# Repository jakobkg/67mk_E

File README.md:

# 67mk_E

[![CC BY-NC-SA 4.0][cc-by-nc-sa-shield]][cc-by-nc-sa]

### A simple "no frills" drop-in replacement PCB for the KBDfans 67mkII / 67lite

---

[KiCAD PCB files](pcb/)

[Gerbers for PCB production](pcb/gerbers/)

[JLCPCB BOM](pcb/fab/67_E_bom_jlc.csv)

[JLCPCB CPL](pcb/fab/67_E_cpl_jlc.csv)

[Vial-QMK firmware](firmware/)

---

---

This work is licensed under a
[Creative Commons Attribution-NonCommercial-ShareAlike 4.0 International License][cc-by-nc-sa].

[![CC BY-NC-SA 4.0][cc-by-nc-sa-image]][cc-by-nc-sa]

[cc-by-nc-sa]: http://creativecommons.org/licenses/by-nc-sa/4.0/
[cc-by-nc-sa-image]: https://licensebuttons.net/l/by-nc-sa/4.0/88x31.png
[cc-by-nc-sa-shield]: https://img.shields.io/badge/License-CC%20BY--NC--SA%204.0-lightgrey.svg

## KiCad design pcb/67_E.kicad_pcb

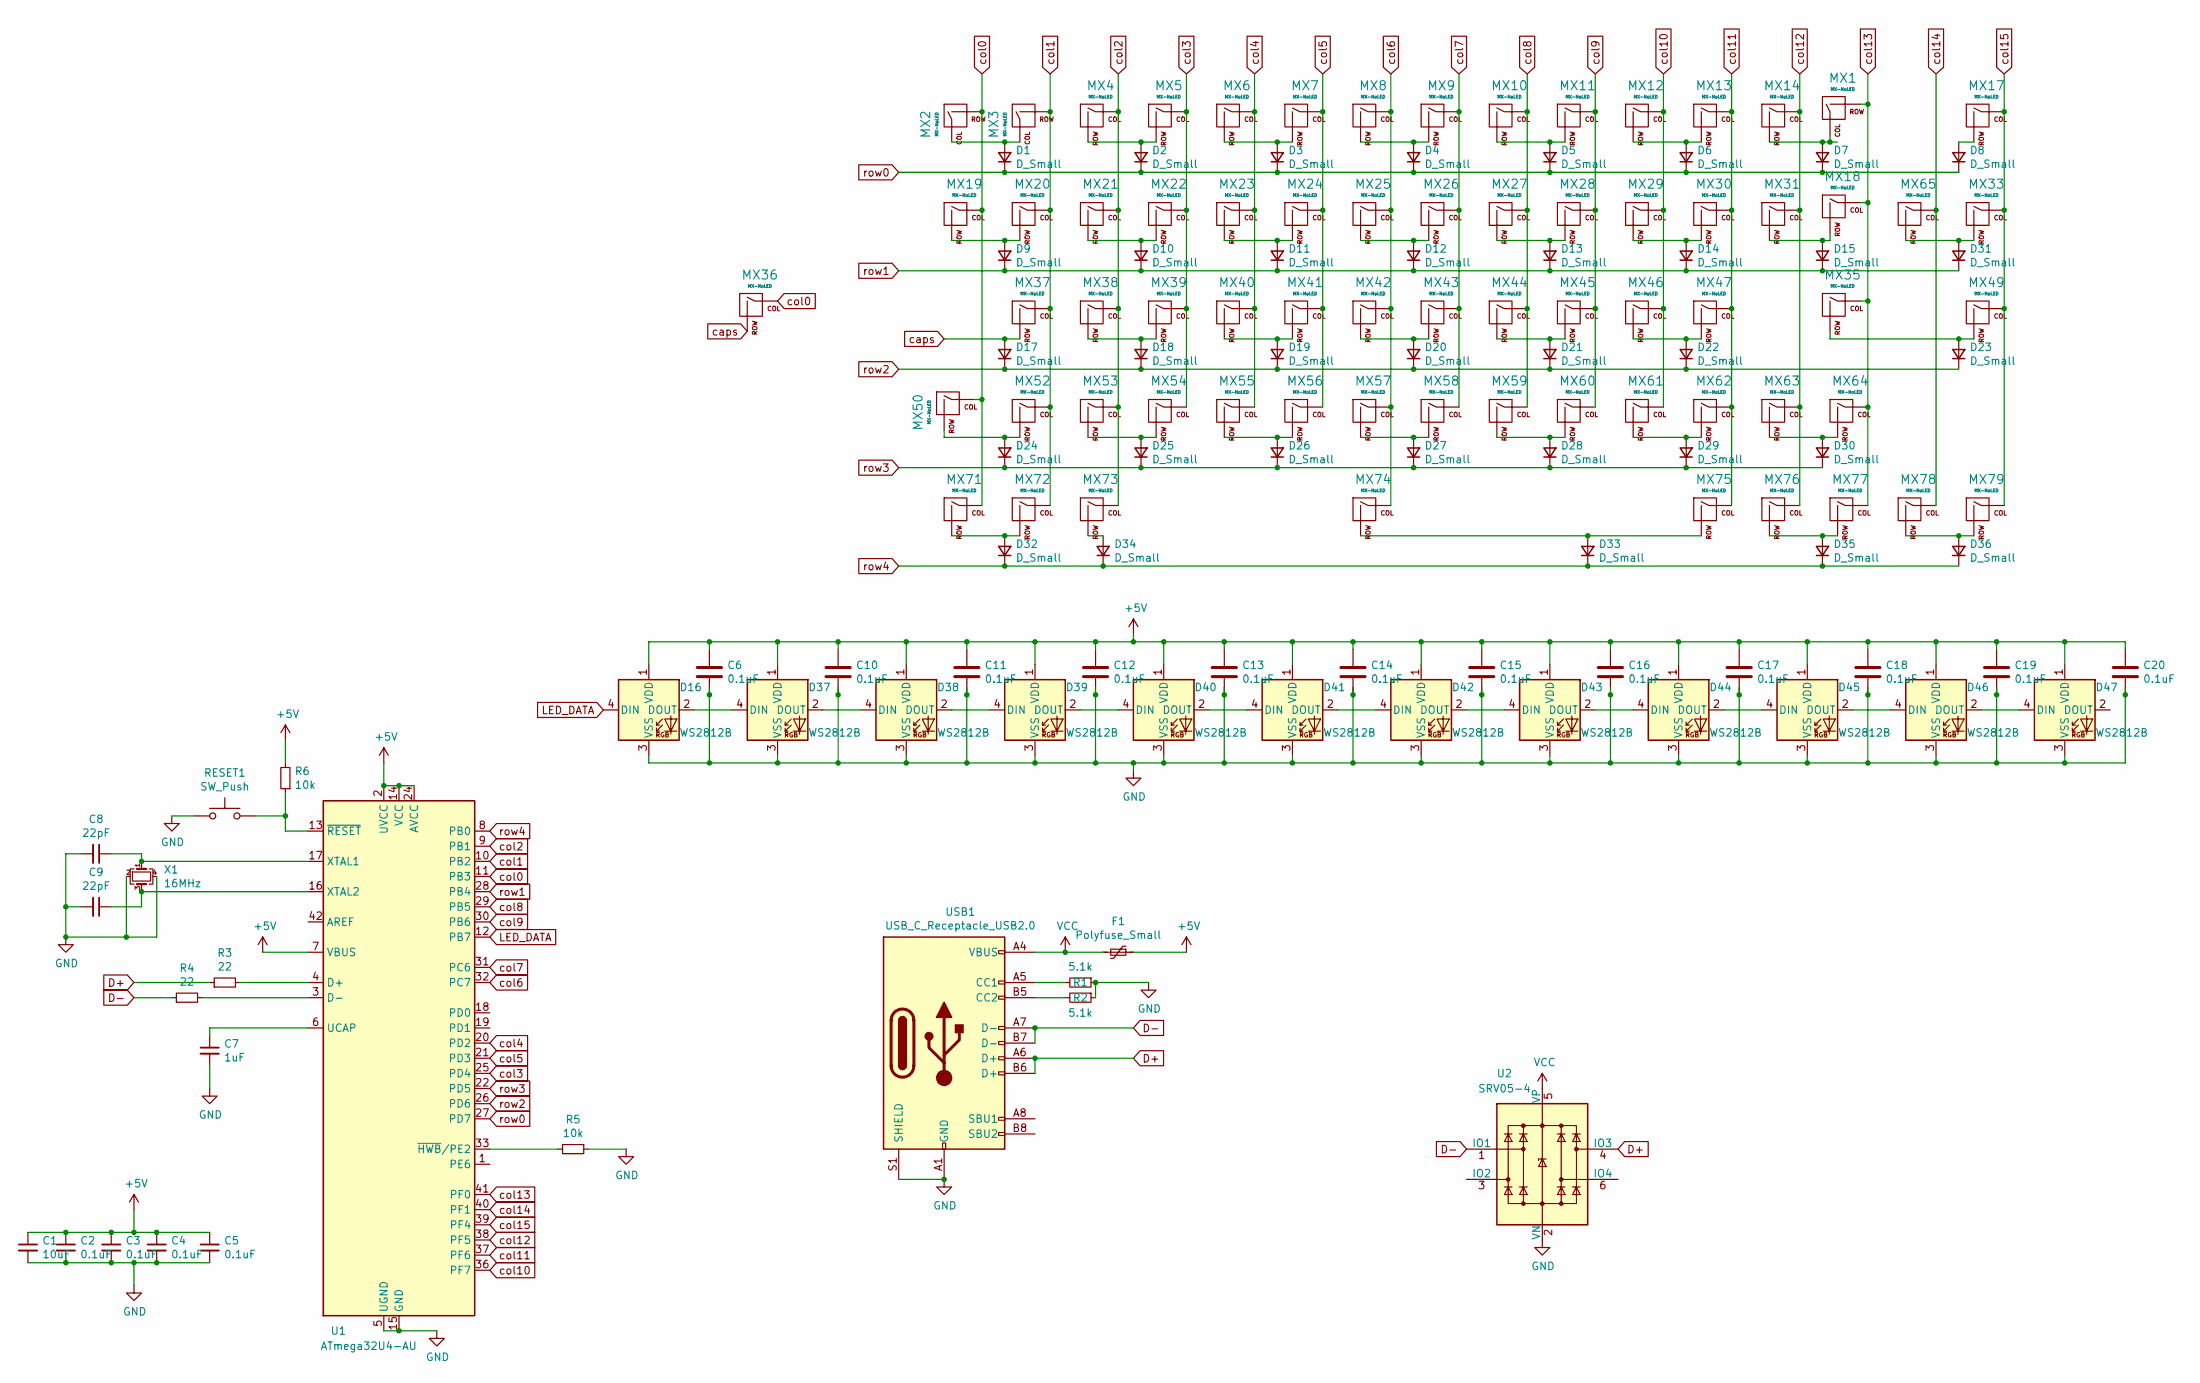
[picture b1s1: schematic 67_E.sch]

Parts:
C1: 10uF; C_0805_2012Metric; LCSC C91245
C2, C3, C4, C5: 0.1uF; C_0805_2012Metric; LCSC C49678
C6, C10, C11, C12, C13, C14, C15, C16, C17, C18, C19, C20: 0.1uF; C_0805_2012Metric
C7: 1uF; C_0805_2012Metric; LCSC C28323
C8, C9: 22pF; C_0805_2012Metric; LCSC C1804
D1, D2, D3, D4, D5, D6, D7, D8, D9, D10, D11, D12, D13, D14, D15, D17, D18, D19, D20, D21, D22, D23, D24, D25, D26, D27, D28, D29, D30, D31, D32, D33, D34, D35, D36: D_Small; D_SOT-23_ANK; LCSC C68978
D16, D37, D38, D39, D40, D41, D42, D43, D44, D45, D46, D47: WS2812B; LED_WS2812B_PLCC4_5.0x5.0mm_P3.2mm
F1: Polyfuse_Small; Fuse_1206_3216Metric; LCSC C69688
MX1: MX-NoLED; MXOnly-2U-Hotswap
MX2, MX3, MX4, MX5, MX6, MX7, MX8, MX9, MX10, MX11, MX12, MX13, MX14, MX17, MX18, MX20, MX21, MX22, MX23, MX24, MX25, MX26, MX27, MX28, MX29, MX30, MX31, MX33, MX37, MX38, MX39, MX40, MX41, MX42, MX43, MX44, MX45, MX46, MX47, MX49, MX52, MX53, MX54, MX55, MX56, MX57, MX58, MX59, MX60, MX61, MX62, MX64, MX65, MX77, MX78, MX79: MX-NoLED; MXOnly-1U-Hotswap
MX19: MX-NoLED; MXOnly-1.5U-Hotswap
MX35: MX-NoLED; MXOnly-ISO-Hotswap-ReversedStabilizers
MX36, MX63: MX-NoLED; MXOnly-1.75U-Hotswap
MX50, MX71, MX72, MX73, MX75, MX76: MX-NoLED; MXOnly-1.25U-Hotswap
MX74: MX-NoLED; MXOnly-6.25U-Hotswap-ReversedStabilizers
R1, R2: 5.1k; R_0805_2012Metric; LCSC C27834
R3, R4: 22; R_0805_2012Metric; LCSC C17561
R5, R6: 10k; R_0805_2012Metric; LCSC C17414
RESET1: SW_Push; TestPoint_2Pads_Pitch2.54mm_Drill0.8mm; LCSC C318884
U1: ATmega32U4-AU; TQFP-44_10x10mm_P0.8mm; LCSC C44854
U2: SRV05-4; SOT-23-6; LCSC C85364
USB1: USB_C_Receptacle_USB2.0; USB_C_Receptacle_HRO_TYPE-C-31-M-12; LCSC C165948
X1: 16MHz; Crystal_SMD_3225-4Pin_3.2x2.5mm; LCSC C13738

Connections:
+5V: C1.1, C2.1, C3.1, C4.1, C5.1, C6.1, C10.1, C11.1, C12.1, C13.1, C14.1, C15.1, C16.1, C17.1, C18.1, C19.1, C20.1, D16.1 (VDD), D37.1 (VDD), D38.1 (VDD), D39.1 (VDD), D40.1 (VDD), D41.1 (VDD), D42.1 (VDD), D43.1 (VDD), D44.1 (VDD), D45.1 (VDD), D46.1 (VDD), D47.1 (VDD), F1.1, R6.2, U1.2 (UVCC), U1.7 (VBUS), U1.14 (VCC), U1.24 (AVCC), U1.34 (VCC), U1.44 (AVCC)
D+: R3.1, U2.4 (IO3), USB1.A6 (D+), USB1.B6 (D+)
D-: R4.1, U2.1 (IO1), USB1.A7 (D-), USB1.B7 (D-)
GND: C1.2, C2.2, C3.2, C4.2, C5.2, C6.2, C7.2, C8.2, C9.2, C10.2, C11.2, C12.2, C13.2, C14.2, C15.2, C16.2, C17.2, C18.2, C19.2, C20.2, D16.3 (VSS), D37.3 (VSS), D38.3 (VSS), D39.3 (VSS), D40.3 (VSS), D41.3 (VSS), D42.3 (VSS), D43.3 (VSS), D44.3 (VSS), D45.3 (VSS), D46.3 (VSS), D47.3 (VSS), R1.1, R2.1, R5.1, RESET1.1, U1.5 (UGND), U1.15 (GND), U1.23 (GND), U1.35 (GND), U1.43 (GND), U2.2 (VN), USB1.A1 (GND), USB1.A12 (GND), USB1.B1 (GND), USB1.B12 (GND), USB1.S1 (SHIELD), X1.2, X1.4
LED_DATA: D16.4 (DIN), U1.12 (PB7)
unnamed: C7.1, U1.6 (UCAP)
unnamed: C8.1, U1.17 (XTAL1), X1.1
unnamed: C9.1, U1.16 (XTAL2), X1.3
unnamed: D1.2 (A), MX2.1 (COL), MX3.1 (COL)
unnamed: D2.2 (A), MX4.2 (ROW), MX5.2 (ROW)
unnamed: D3.2 (A), MX6.2 (ROW), MX7.2 (ROW)
unnamed: D4.2 (A), MX8.2 (ROW), MX9.2 (ROW)
unnamed: D5.2 (A), MX10.2 (ROW), MX11.2 (ROW)
unnamed: D6.2 (A), MX12.2 (ROW), MX13.2 (ROW)
unnamed: D7.2 (A), MX1.1 (COL), MX14.2 (ROW)
unnamed: D8.2 (A), MX17.2 (ROW)
unnamed: D9.2 (A), MX19.2 (ROW), MX20.2 (ROW)
unnamed: D10.2 (A), MX21.2 (ROW), MX22.2 (ROW)
unnamed: D11.2 (A), MX23.2 (ROW), MX24.2 (ROW)
unnamed: D12.2 (A), MX25.2 (ROW), MX26.2 (ROW)
unnamed: D13.2 (A), MX27.2 (ROW), MX28.2 (ROW)
unnamed: D14.2 (A), MX29.2 (ROW), MX30.2 (ROW)
unnamed: D15.2 (A), MX18.2 (ROW), MX31.2 (ROW)
unnamed: D16.2 (DOUT), D37.4 (DIN)
unnamed: D18.2 (A), MX38.2 (ROW), MX39.2 (ROW)
unnamed: D19.2 (A), MX40.2 (ROW), MX41.2 (ROW)
unnamed: D20.2 (A), MX42.2 (ROW), MX43.2 (ROW)
unnamed: D21.2 (A), MX44.2 (ROW), MX45.2 (ROW)
unnamed: D22.2 (A), MX46.2 (ROW), MX47.2 (ROW)
unnamed: D23.2 (A), MX35.2 (ROW), MX49.2 (ROW)
unnamed: D24.2 (A), MX50.2 (ROW), MX52.2 (ROW)
unnamed: D25.2 (A), MX53.2 (ROW), MX54.2 (ROW)
unnamed: D26.2 (A), MX55.2 (ROW), MX56.2 (ROW)
unnamed: D27.2 (A), MX57.2 (ROW), MX58.2 (ROW)
unnamed: D28.2 (A), MX59.2 (ROW), MX60.2 (ROW)
unnamed: D29.2 (A), MX61.2 (ROW), MX62.2 (ROW)
unnamed: D30.2 (A), MX63.2 (ROW), MX64.2 (ROW)
unnamed: D31.2 (A), MX33.2 (ROW), MX65.2 (ROW)
unnamed: D32.2 (A), MX71.2 (ROW), MX72.2 (ROW)
unnamed: D33.2 (A), MX74.2 (ROW), MX75.2 (ROW)
unnamed: D34.2 (A), MX73.2 (ROW)
unnamed: D35.2 (A), MX76.2 (ROW), MX77.2 (ROW)
unnamed: D36.2 (A), MX78.2 (ROW), MX79.2 (ROW)
unnamed: D37.2 (DOUT), D38.4 (DIN)
unnamed: D38.2 (DOUT), D39.4 (DIN)
unnamed: D39.2 (DOUT), D40.4 (DIN)
unnamed: D40.2 (DOUT), D41.4 (DIN)
unnamed: D41.2 (DOUT), D42.4 (DIN)
unnamed: D42.2 (DOUT), D43.4 (DIN)
unnamed: D43.2 (DOUT), D44.4 (DIN)
unnamed: D44.2 (DOUT), D45.4 (DIN)
unnamed: D45.2 (DOUT), D46.4 (DIN)
unnamed: D46.2 (DOUT), D47.4 (DIN)
unnamed: R1.2, USB1.A5 (CC1)
unnamed: R2.2, USB1.B5 (CC2)
unnamed: R3.2, U1.4 (D+)
unnamed: R4.2, U1.3 (D-)
unnamed: R5.2, U1.33 (~HWB~/PE2)
unnamed: R6.1, RESET1.2, U1.13 (~RESET)
VCC: F1.2, U2.5 (VP), USB1.A4 (VBUS), USB1.A9 (VBUS), USB1.B4 (VBUS), USB1.B9 (VBUS)
caps: D17.2 (A), MX36.2 (ROW), MX37.2 (ROW)
col0: MX2.2 (ROW), MX19.1 (COL), MX36.1 (COL), MX50.1 (COL), MX71.1 (COL), U1.11 (PB3)
col1: MX3.2 (ROW), MX20.1 (COL), MX37.1 (COL), MX52.1 (COL), MX72.1 (COL), U1.10 (PB2)
col2: MX4.1 (COL), MX21.1 (COL), MX38.1 (COL), MX53.1 (COL), MX73.1 (COL), U1.9 (PB1)
col3: MX5.1 (COL), MX22.1 (COL), MX39.1 (COL), MX54.1 (COL), U1.25 (PD4)
col4: MX6.1 (COL), MX23.1 (COL), MX40.1 (COL), MX55.1 (COL), U1.20 (PD2)
col5: MX7.1 (COL), MX24.1 (COL), MX41.1 (COL), MX56.1 (COL), U1.21 (PD3)
col6: MX8.1 (COL), MX25.1 (COL), MX42.1 (COL), MX57.1 (COL), MX74.1 (COL), U1.32 (PC7)
col7: MX9.1 (COL), MX26.1 (COL), MX43.1 (COL), MX58.1 (COL), U1.31 (PC6)
col8: MX10.1 (COL), MX27.1 (COL), MX44.1 (COL), MX59.1 (COL), U1.29 (PB5)
col9: MX11.1 (COL), MX28.1 (COL), MX45.1 (COL), MX60.1 (COL), U1.30 (PB6)
col10: MX12.1 (COL), MX29.1 (COL), MX46.1 (COL), MX61.1 (COL), U1.36 (PF7)
col11: MX13.1 (COL), MX30.1 (COL), MX47.1 (COL), MX62.1 (COL), MX75.1 (COL), U1.37 (PF6)
col12: MX14.1 (COL), MX31.1 (COL), MX63.1 (COL), MX76.1 (COL), U1.38 (PF5)
col13: MX1.2 (ROW), MX18.1 (COL), MX35.1 (COL), MX64.1 (COL), MX77.1 (COL), U1.41 (PF0)
col14: MX65.1 (COL), MX78.1 (COL), U1.40 (PF1)
col15: MX17.1 (COL), MX33.1 (COL), MX49.1 (COL), MX79.1 (COL), U1.39 (PF4)
row0: D1.1 (K), D2.1 (K), D3.1 (K), D4.1 (K), D5.1 (K), D6.1 (K), D7.1 (K), D8.1 (K), U1.27 (PD7)
row1: D9.1 (K), D10.1 (K), D11.1 (K), D12.1 (K), D13.1 (K), D14.1 (K), D15.1 (K), D31.1 (K), U1.28 (PB4)
row2: D17.1 (K), D18.1 (K), D19.1 (K), D20.1 (K), D21.1 (K), D22.1 (K), D23.1 (K), U1.26 (PD6)
row3: D24.1 (K), D25.1 (K), D26.1 (K), D27.1 (K), D28.1 (K), D29.1 (K), D30.1 (K), U1.22 (PD5)
row4: D32.1 (K), D33.1 (K), D34.1 (K), D35.1 (K), D36.1 (K), U1.8 (PB0)

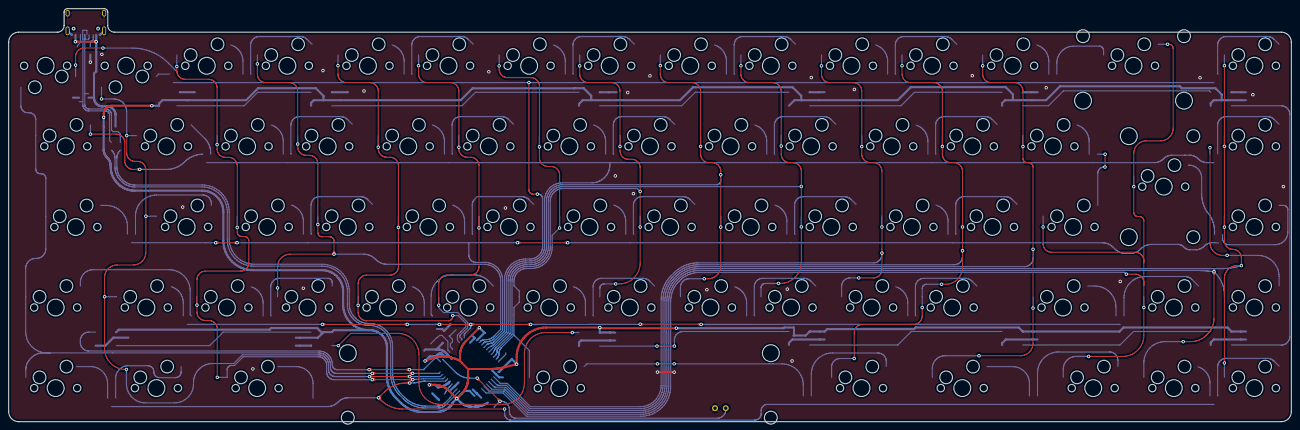
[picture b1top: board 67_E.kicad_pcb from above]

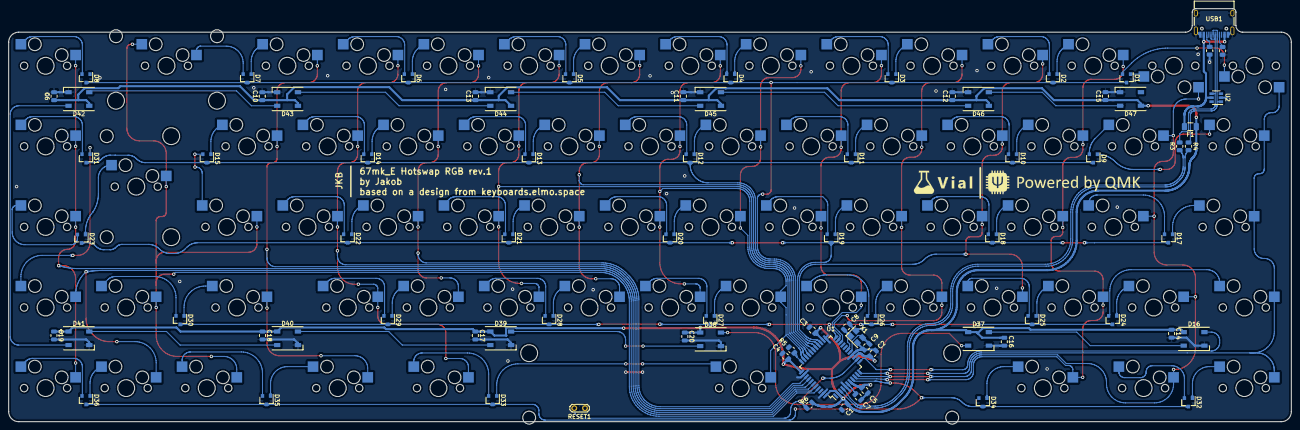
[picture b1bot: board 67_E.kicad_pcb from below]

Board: 2 copper layers, 303.2 x 97.6 mm, 147 parts (79 on the bottom side), 82 nets.

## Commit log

2021-08-12 replace all switch footprints with hotswap equivalents and begin re-routing PCB
2021-08-13 Re-trace USB port, fuse and ESD
2021-08-14 finish rerouting switch matrix
2021-08-14 remove unused LED footprint
2021-08-15 Add RGB underglow to PCB
2021-08-15 remove unneeded backup/cache files
